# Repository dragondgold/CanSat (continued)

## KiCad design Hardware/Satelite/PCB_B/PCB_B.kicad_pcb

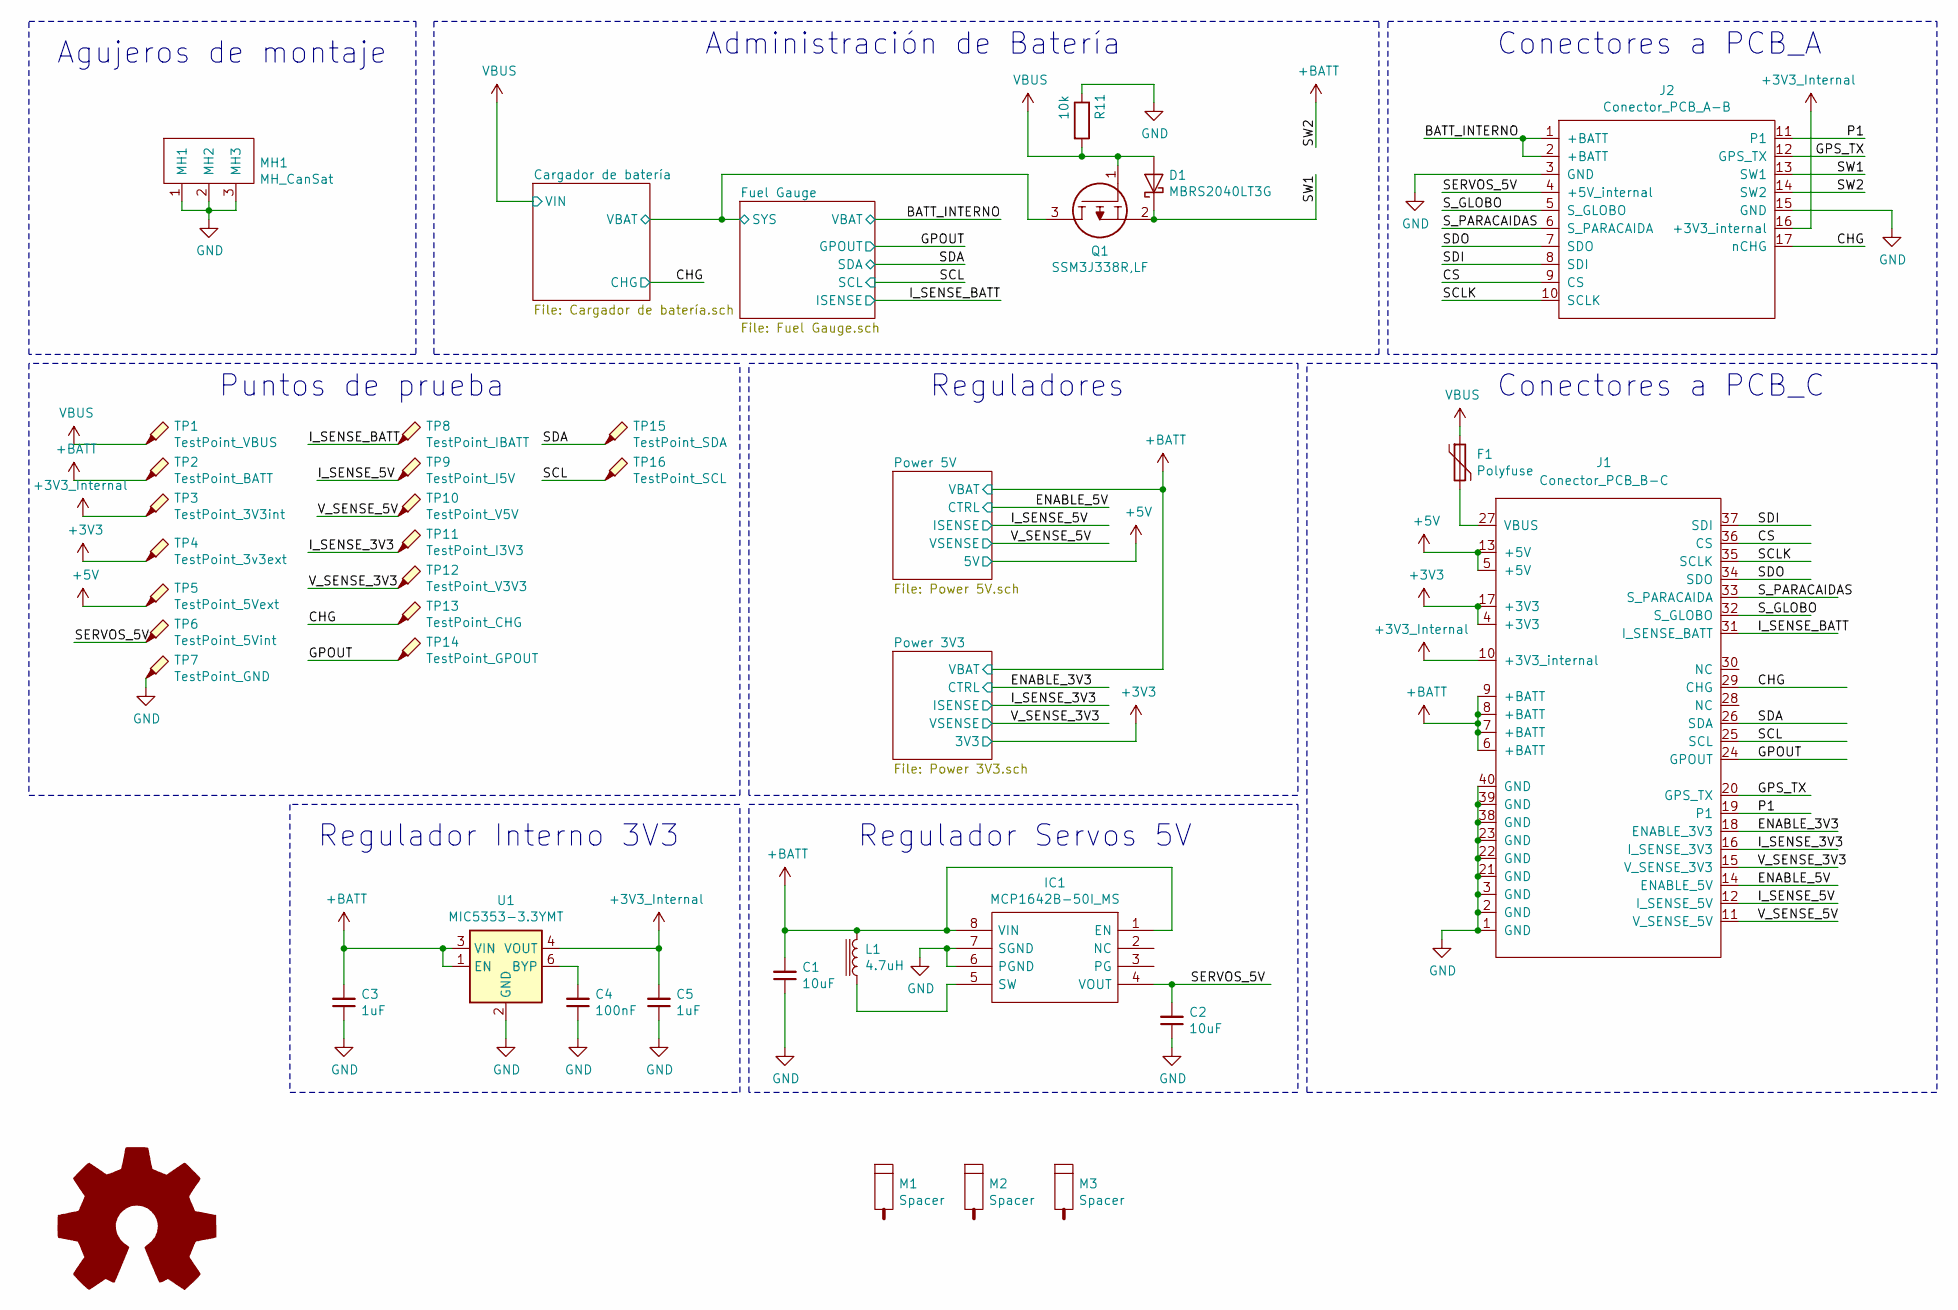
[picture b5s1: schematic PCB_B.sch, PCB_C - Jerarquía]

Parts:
C1, C2: 10uF; C_0805_2012Metric_Pad1.15x1.40mm_HandSolder; Voltage 10V; Manufacturer Part Number C2012X7R1A106M125AC
C3, C5: 1uF; C_0603_1608Metric_Pad1.05x0.95mm_HandSolder; Voltage 10V; Manufacturer Part Number LMK107B7105MA-T
C4: 100nF; C_0603_1608Metric_Pad1.05x0.95mm_HandSolder; Voltage 10V; Manufacturer Part Number EMK107B7104KAHT
D1: MBRS2040LT3G; D_SMB; Manufacturer Part Number MBRS2040LT3G
F1: Polyfuse; Fuse_1812_4532Metric_Pad1.30x3.40mm_HandSolder; Manufacturer Part Number 0ZCG0050AF2C
IC1: MCP1642B-50I_MS; SOP65P490X110-8N; Manufacturer Part Number MCP1642B-50I/MS
J1: Conector_PCB_B-C; Conector_PCB_B-C_Lado_B; Manufacturer Part Number 52465-2071
J2: Conector_PCB_A-B; Manufacturer Part Number CES-103-01-T-S
L1: 4.7uH; SRN3010TA-4R7M; Manufacturer Part Number SRN3010TA-4R7M
M1, M2, M3: Spacer; Empty_Footprint; Manufacturer Part Number R30-3011202
MH1: MH_CanSat
Q1: SSM3J338R,LF; SSM3J332RLFT; Manufacturer Part Number SSM3J338R,LF
R11: 10k; C_0603_1608Metric_Pad1.05x0.95mm_HandSolder; Manufacturer Part Number RC0603JR-0710KL
TP1: TestPoint_VBUS; TestPoint_Pad_D1.0mm
TP2: TestPoint_BATT; TestPoint_Pad_D1.0mm
TP3: TestPoint_3V3int; TestPoint_Pad_D1.0mm
TP4: TestPoint_3v3ext; TestPoint_Pad_D1.0mm
TP5: TestPoint_5Vext; TestPoint_Pad_D1.0mm
TP6: TestPoint_5Vint; TestPoint_Pad_D1.0mm
TP7: TestPoint_GND; TestPoint_THTPad_1.0x1.0mm_Drill0.5mm
TP8: TestPoint_IBATT; TestPoint_Pad_D1.0mm
TP9: TestPoint_I5V; TestPoint_Pad_D1.0mm
TP10: TestPoint_V5V; TestPoint_Pad_D1.0mm
TP11: TestPoint_I3V3; TestPoint_Pad_D1.0mm
TP12: TestPoint_V3V3; TestPoint_Pad_D1.0mm
TP13: TestPoint_CHG; TestPoint_Pad_D1.0mm
TP14: TestPoint_GPOUT; TestPoint_Pad_D1.0mm
TP15: TestPoint_SDA; TestPoint_Pad_D1.0mm
TP16: TestPoint_SCL; TestPoint_Pad_D1.0mm
U1: MIC5353-3.3YMT; MLF-6-1EP_1.6x1.6mm_P0.5mm_EP0.5x1.26mm; Manufacturer Part Number MIC5353-3.3YMT-TR

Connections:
+3V3: J1.4 (+3V3), J1.17 (+3V3), TP4.1; also elsewhere on the board
+3V3_Internal: C5.2, J1.10 (+3V3_internal), J2.16 (+3V3_internal), TP3.1, U1.4 (VOUT); also elsewhere on the board
+5V: J1.5 (+5V), J1.13 (+5V), TP5.1; also elsewhere on the board
+BATT: C1.2, C3.2, IC1.1 (EN), IC1.8 (VIN), J1.6 (+BATT), J1.7 (+BATT), J1.8 (+BATT), J1.9 (+BATT), J2.14 (SW2), L1.2, TP2.1, U1.1 (EN), U1.3 (VIN); also elsewhere on the board
/BATT_INTERNO: J2.1 (+BATT), J2.2 (+BATT); also elsewhere on the board
/CHG: J1.29 (CHG), J2.17 (nCHG), TP13.1; also elsewhere on the board
/CS: J1.36 (CS), J2.9 (CS)
/ENABLE_3V3: J1.18 (ENABLE_3V3); also elsewhere on the board
/ENABLE_5V: J1.14 (ENABLE_5V); also elsewhere on the board
/Fuel Gauge/SYS: Q1.3; also elsewhere on the board
/GPOUT: J1.24 (GPOUT), TP14.1; also elsewhere on the board
/GPS_TX: J1.20 (GPS_TX), J2.12 (GPS_TX)
/I_SENSE_3V3: J1.16 (I_SENSE_3V3), TP11.1; also elsewhere on the board
/I_SENSE_5V: J1.12 (I_SENSE_5V), TP9.1; also elsewhere on the board
/I_SENSE_BATT: J1.31 (I_SENSE_BATT), TP8.1; also elsewhere on the board
/P1: J1.19 (P1), J2.11 (P1)
/SCL: J1.25 (SCL), TP16.1; also elsewhere on the board
/SCLK: J1.35 (SCLK), J2.10 (SCLK)
/SDA: J1.26 (SDA), TP15.1; also elsewhere on the board
/SDI: J1.37 (SDI), J2.8 (SDI)
/SDO: J1.34 (SDO), J2.7 (SDO)
/SERVOS_5V: C2.2, IC1.4 (VOUT), J2.4 (+5V_internal), TP6.1
/SW1: D1.1 (K), J2.13 (SW1), Q1.2
/S_GLOBO: J1.32 (S_GLOBO), J2.5 (S_GLOBO)
/S_PARACAIDAS: J1.33 (S_PARACAIDA), J2.6 (S_PARACAIDA)
/V_SENSE_3V3: J1.15 (V_SENSE_3V3), TP12.1; also elsewhere on the board
/V_SENSE_5V: J1.11 (V_SENSE_5V), TP10.1; also elsewhere on the board
GND: C1.1, C2.1, C3.1, C4.1, C5.1, IC1.6 (PGND), IC1.7 (SGND), J1.1 (GND), J1.2 (GND), J1.3 (GND), J1.21 (GND), J1.22 (GND), J1.23 (GND), J1.38 (GND), J1.39 (GND), J1.40 (GND), J2.3 (GND), J2.15 (GND), MH1.1 (MH1), MH1.2 (MH2), MH1.3 (MH3), R11.1, TP7.1, U1.2 (GND), U1.7 (GND); also elsewhere on the board
unnamed: C4.2, U1.6 (BYP)
unnamed: F1.2, J1.27 (VBUS)
unnamed: IC1.5 (SW), L1.1
VBUS: D1.2 (A), F1.1, Q1.1, R11.2, TP1.1; also elsewhere on the board

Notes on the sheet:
Conectores a PCB_A
Reguladores
Regulador Interno 3V3
Administración de Batería
Conectores a PCB_C
Regulador Servos 5V
Agujeros de montaje
Puntos de prueba

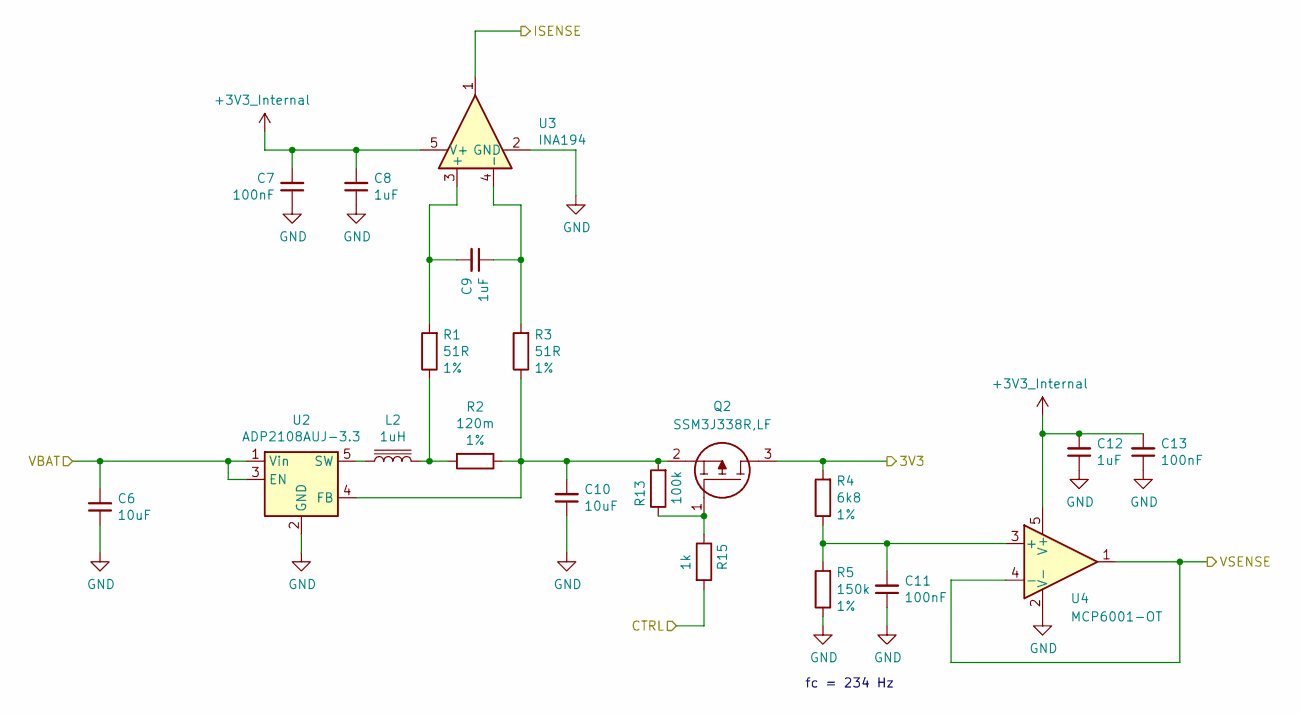
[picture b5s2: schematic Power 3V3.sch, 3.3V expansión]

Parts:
C6, C10: 10uF; C_0805_2012Metric_Pad1.15x1.40mm_HandSolder; Voltage 10V; Manufacturer Part Number C2012X7R1A106M125AC
C7, C11, C13: 100nF; C_0603_1608Metric_Pad1.05x0.95mm_HandSolder; Voltage 10V; Manufacturer Part Number EMK107B7104KAHT
C8, C9, C12: 1uF; C_0603_1608Metric_Pad1.05x0.95mm_HandSolder; Voltage 10V; Manufacturer Part Number LMK107B7105MA-T
L2: 1uH; L_0805_2012Metric_Pad1.15x1.40mm_HandSolder; Manufacturer Part Number LQM21PN1R0MC0D
Q2: SSM3J338R,LF; SSM3J332RLFT; Manufacturer Part Number SSM3J338R,LF
R1, R3: 51R; R_0603_1608Metric_Pad1.05x0.95mm_HandSolder; Tolerance 1%; Manufacturer Part Number AC0603FR-0751RL
R2: 120m; R_1206_3216Metric_Pad1.42x1.75mm_HandSolder; Tolerance 1%; Manufacturer Part Number KRL1632E-M-R120-F-T5
R4: 6k8; R_0603_1608Metric_Pad1.05x0.95mm_HandSolder; Tolerance 1%; Manufacturer Part Number RC0603FR-076K8L
R5: 150k; R_0603_1608Metric_Pad1.05x0.95mm_HandSolder; Tolerance 1%; Manufacturer Part Number RC0603FR-07150KL
R13: 100k; R_0603_1608Metric_Pad1.05x0.95mm_HandSolder; Manufacturer Part Number RC0603JR-07100KL
R15: 1k; C_0603_1608Metric_Pad1.05x0.95mm_HandSolder; Manufacturer Part Number RC0603JR-071KL
U2: ADP2108AUJ-3.3; TSOT-23-5; Manufacturer Part Number ADP2108AUJZ-3.3-R7
U3: INA194; SOT-23-5; Manufacturer Part Number INA194AIDBVR
U4: MCP6001-OT; SOT-23-5; Manufacturer Part Number MCP6001T-I/OT

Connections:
+3V3: Q2.3, R4.2; also elsewhere on the board
+3V3_Internal: C7.2, C8.2, C12.2, C13.2, U3.5 (V+), U4.5 (V+); also elsewhere on the board
+BATT: C6.2, U2.1 (Vin), U2.3 (EN); also elsewhere on the board
/ENABLE_3V3: R15.2; also elsewhere on the board
/I_SENSE_3V3: U3.1; also elsewhere on the board
/V_SENSE_3V3: U4.1, U4.4 (-); also elsewhere on the board
GND: C6.1, C7.1, C8.1, C10.1, C11.1, C12.1, C13.1, R5.1, U2.2 (GND), U3.2 (GND), U4.2 (V-); also elsewhere on the board
unnamed: C9.1, R3.2, U3.4 (-)
unnamed: C9.2, R1.2, U3.3 (+)
unnamed: C10.2, Q2.2, R2.1, R3.1, R13.2, U2.4 (FB)
unnamed: C11.2, R4.1, R5.2, U4.3 (+)
unnamed: L2.1, U2.5 (SW)
unnamed: L2.2, R1.1, R2.2
unnamed: Q2.1, R13.1, R15.1

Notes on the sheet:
fc = 234 Hz

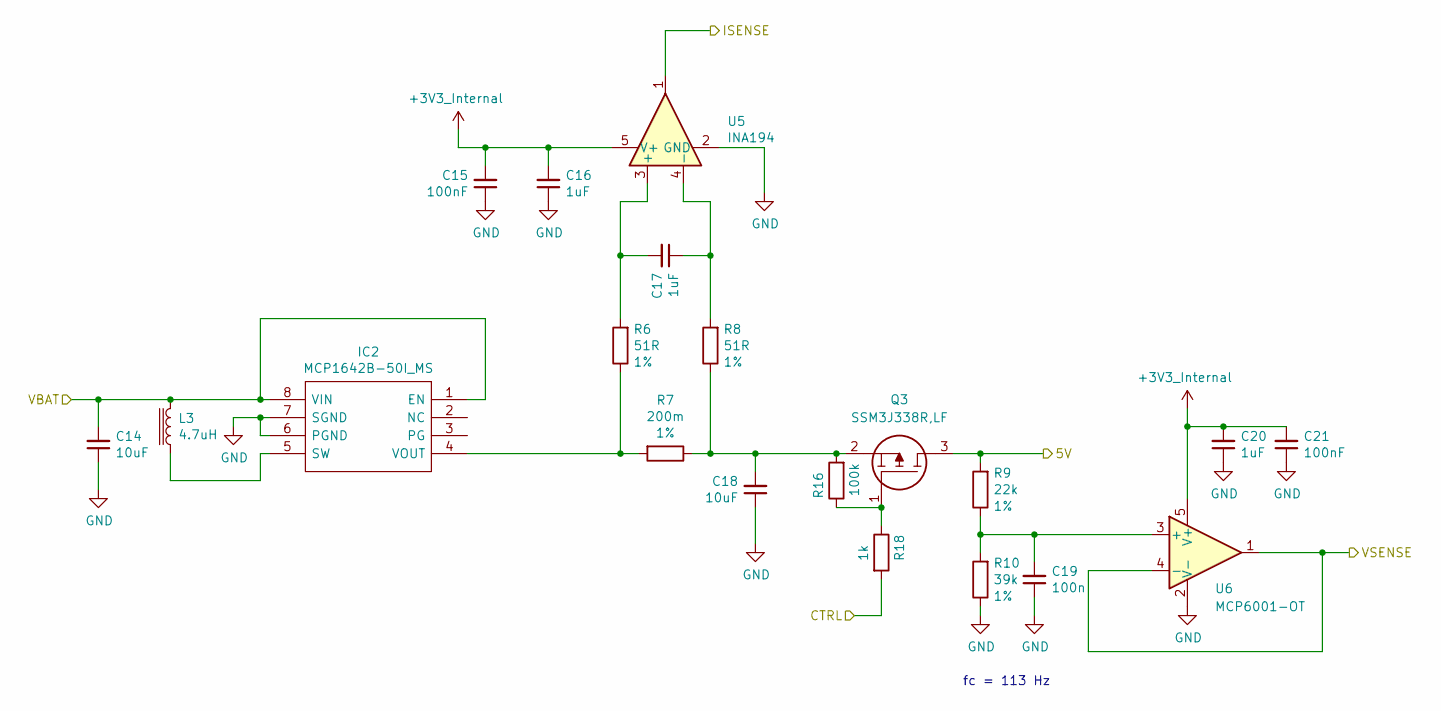
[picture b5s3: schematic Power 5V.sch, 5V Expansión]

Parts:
C14, C18: 10uF; C_0805_2012Metric_Pad1.15x1.40mm_HandSolder; Voltage 10V; Manufacturer Part Number C2012X7R1A106M125AC
C15, C21: 100nF; C_0603_1608Metric_Pad1.05x0.95mm_HandSolder; Voltage 10V; Manufacturer Part Number EMK107B7104KAHT
C16, C17, C20: 1uF; C_0603_1608Metric_Pad1.05x0.95mm_HandSolder; Voltage 10V; Manufacturer Part Number LMK107B7105MA-T
C19: 100n; C_0603_1608Metric_Pad1.05x0.95mm_HandSolder; Voltage 10V; Manufacturer Part Number EMK107B7104KAHT
IC2: MCP1642B-50I_MS; SOP65P490X110-8N; Manufacturer Part Number MCP1642B-50I/MS
L3: 4.7uH; SRN3010TA-4R7M; Manufacturer Part Number SRN3010TA-4R7M
Q3: SSM3J338R,LF; SSM3J332RLFT; Manufacturer Part Number SSM3J338R,LF
R6, R8: 51R; R_0603_1608Metric_Pad1.05x0.95mm_HandSolder; Tolerance 1%; Manufacturer Part Number AC0603FR-0751RL
R7: 200m; R_1206_3216Metric_Pad1.42x1.75mm_HandSolder; Tolerance 1%; Manufacturer Part Number KRL1632E-C-R200-F-T5
R9: 22k; R_0603_1608Metric_Pad1.05x0.95mm_HandSolder; Tolerance 1%; Manufacturer Part Number RC0603FR-1322KL
R10: 39k; R_0603_1608Metric_Pad1.05x0.95mm_HandSolder; Tolerance 1%; Manufacturer Part Number RC0603FR-1339KL
R16: 100k; R_0603_1608Metric_Pad1.05x0.95mm_HandSolder; Manufacturer Part Number RC0603JR-07100KL
R18: 1k; C_0603_1608Metric_Pad1.05x0.95mm_HandSolder; Manufacturer Part Number RC0603JR-071KL
U5: INA194; SOT-23-5; Manufacturer Part Number INA194AIDBVR
U6: MCP6001-OT; SOT-23-5; Manufacturer Part Number MCP6001T-I/OT

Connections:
+3V3_Internal: C15.2, C16.2, C20.2, C21.2, U5.5 (V+), U6.5 (V+); also elsewhere on the board
+5V: Q3.3, R9.2; also elsewhere on the board
+BATT: C14.2, IC2.1 (EN), IC2.8 (VIN), L3.2; also elsewhere on the board
/ENABLE_5V: R18.2; also elsewhere on the board
/I_SENSE_5V: U5.1; also elsewhere on the board
/V_SENSE_5V: U6.1, U6.4 (-); also elsewhere on the board
GND: C14.1, C15.1, C16.1, C18.1, C19.1, C20.1, C21.1, IC2.6 (PGND), IC2.7 (SGND), R10.1, U5.2 (GND), U6.2 (V-); also elsewhere on the board
unnamed: C17.1, R8.2, U5.4 (-)
unnamed: C17.2, R6.2, U5.3 (+)
unnamed: C18.2, Q3.2, R7.1, R8.1, R16.2
unnamed: C19.2, R9.1, R10.2, U6.3 (+)
unnamed: IC2.4 (VOUT), R6.1, R7.2
unnamed: IC2.5 (SW), L3.1
unnamed: Q3.1, R16.1, R18.1

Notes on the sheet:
fc = 113 Hz

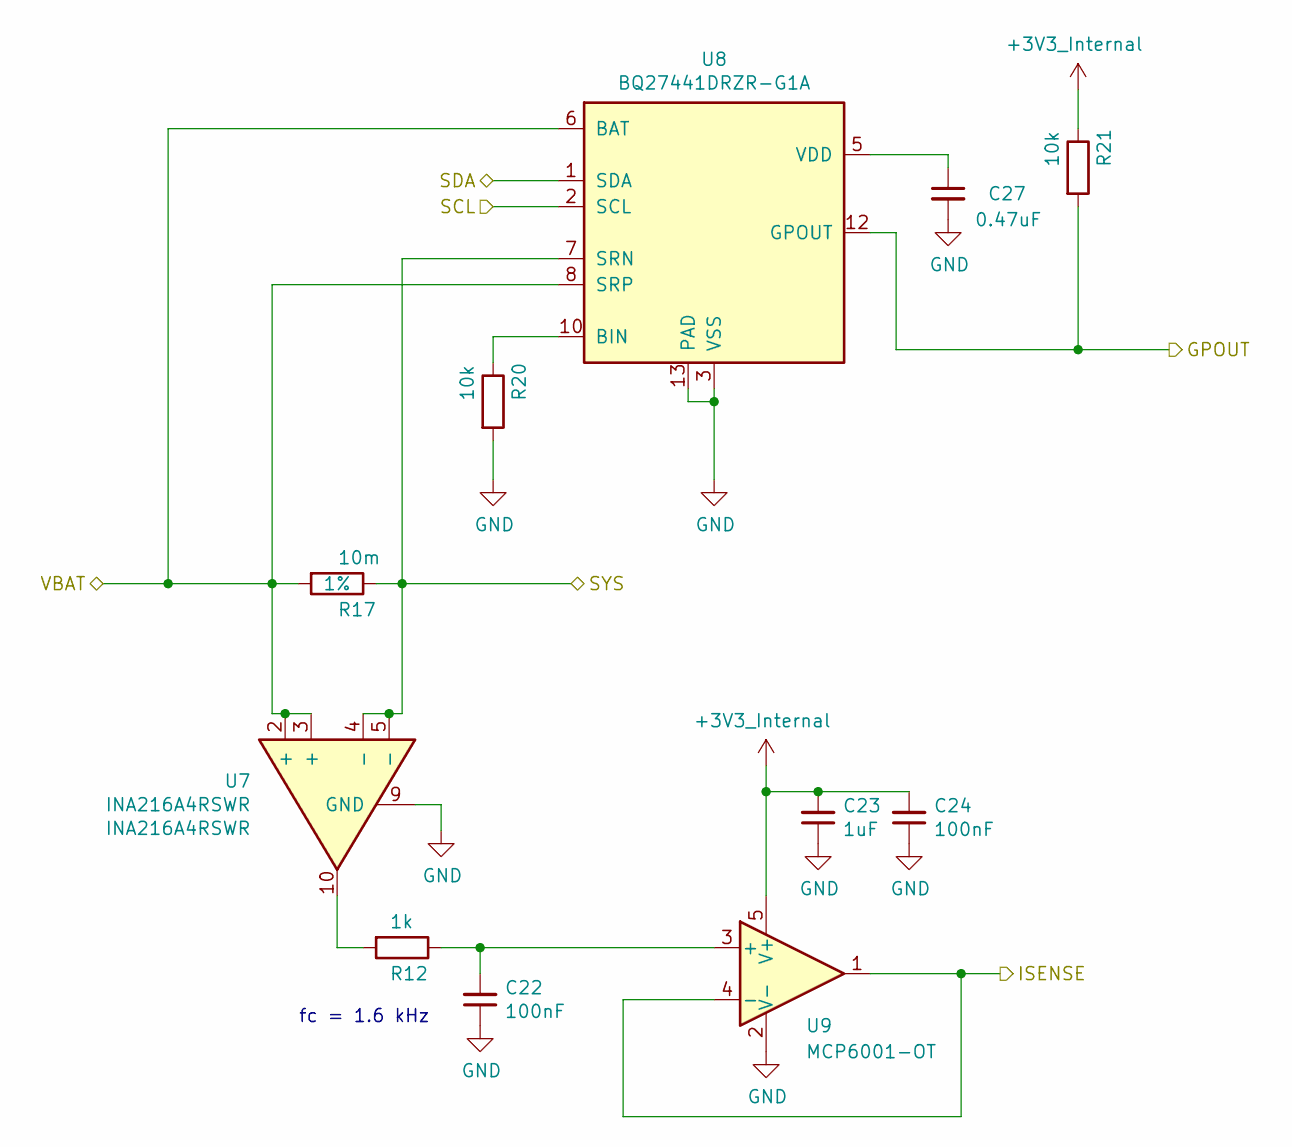
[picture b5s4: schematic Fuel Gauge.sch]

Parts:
C22, C24: 100nF; C_0603_1608Metric_Pad1.05x0.95mm_HandSolder; Voltage 10V; Manufacturer Part Number EMK107B7104KAHT
C23: 1uF; C_0603_1608Metric_Pad1.05x0.95mm_HandSolder; Voltage 10V; Manufacturer Part Number LMK107B7105MA-T
C27: 0.47uF; C_0603_1608Metric_Pad1.05x0.95mm_HandSolder; Manufacturer Part Number 885012206024
R12: 1k; C_0603_1608Metric_Pad1.05x0.95mm_HandSolder; Manufacturer Part Number RC0603JR-071KL
R17: 10m; R_2512_6332Metric_Pad1.52x3.35mm_HandSolder; Tolerance 1%; Manufacturer Part Number KRL3264-C-R010-F-T1
R20, R21: 10k; C_0603_1608Metric_Pad1.05x0.95mm_HandSolder; Manufacturer Part Number RC0603JR-0710KL
U7: INA216A4RSWR; UQFN-10_1.3x1.8mm_P0.4mm; Manufacturer Part Number INA216A4RSWR
U8: BQ27441DRZR-G1A; Texas_S-PDSO-N12; Manufacturer Part Number BQ27441DRZR-G1A
U9: MCP6001-OT; SOT-23-5; Manufacturer Part Number MCP6001T-I/OT

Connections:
+3V3_Internal: C23.2, C24.2, R21.1, U9.5 (V+); also elsewhere on the board
/BATT_INTERNO: R17.2, U7.2 (+), U7.3 (+), U8.6 (BAT), U8.8 (SRP); also elsewhere on the board
/Fuel Gauge/SYS: R17.1, U7.4 (-), U7.5 (-), U8.7 (SRN); also elsewhere on the board
/GPOUT: R21.2, U8.12 (GPOUT); also elsewhere on the board
/I_SENSE_BATT: U9.1, U9.4 (-); also elsewhere on the board
/SCL: U8.2 (SCL); also elsewhere on the board
/SDA: U8.1 (SDA); also elsewhere on the board
GND: C22.1, C23.1, C24.1, C27.2, R20.2, U7.9 (GND), U8.3 (VSS), U8.13 (PAD), U9.2 (V-); also elsewhere on the board
unnamed: C22.2, R12.1, U9.3 (+)
unnamed: C27.1, U8.5 (VDD)
unnamed: R12.2, U7.10
unnamed: R20.1, U8.10 (BIN)

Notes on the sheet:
fc = 1.6 kHz

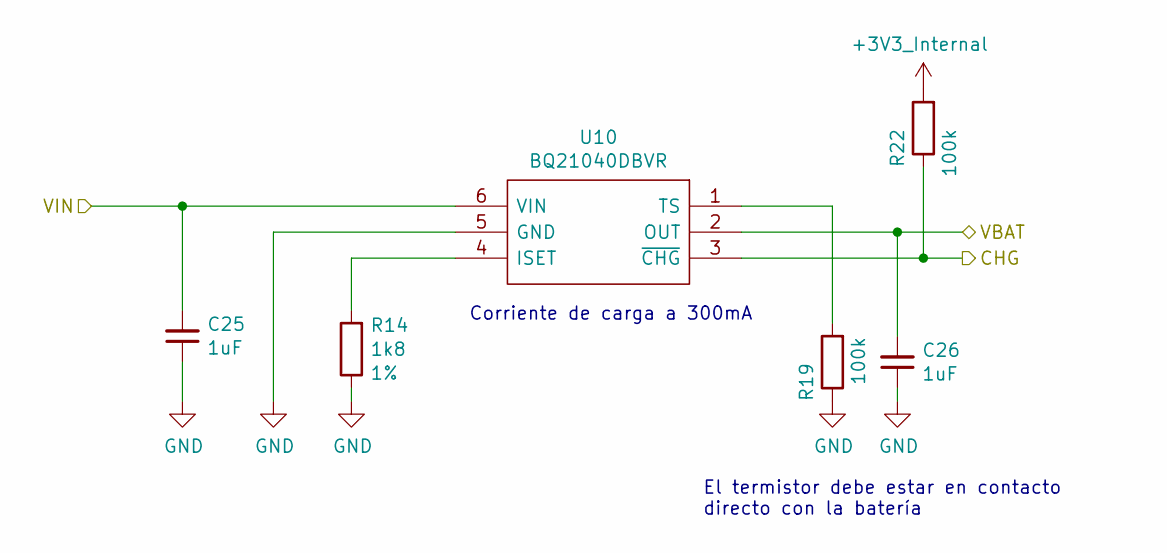
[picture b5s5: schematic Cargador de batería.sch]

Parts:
C25, C26: 1uF; C_0603_1608Metric_Pad1.05x0.95mm_HandSolder; Voltage 10V; Manufacturer Part Number LMK107B7105MA-T
R14: 1k8; R_0603_1608Metric_Pad1.05x0.95mm_HandSolder; Tolerance 1%; Manufacturer Part Number RC0603FR-071K8L
R19, R22: 100k; R_0603_1608Metric_Pad1.05x0.95mm_HandSolder; Manufacturer Part Number RC0603JR-07100KL
U10: BQ21040DBVR; SOT95P280X145-6N; Manufacturer_Part_Number BQ21040DBVR; Mouser Part Number 595-BQ21040DBVR

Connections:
+3V3_Internal: R22.2; also elsewhere on the board
/CHG: R22.1, U10.3 (~CHG); also elsewhere on the board
/Fuel Gauge/SYS: C26.2, U10.2 (OUT); also elsewhere on the board
GND: C25.1, C26.1, R14.1, R19.1, U10.5 (GND); also elsewhere on the board
unnamed: R14.2, U10.4 (ISET)
unnamed: R19.2, U10.1 (TS)
VBUS: C25.2, U10.6 (VIN); also elsewhere on the board

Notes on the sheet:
Corriente de carga a 300mA
El termistor debe estar en contacto directo con la batería

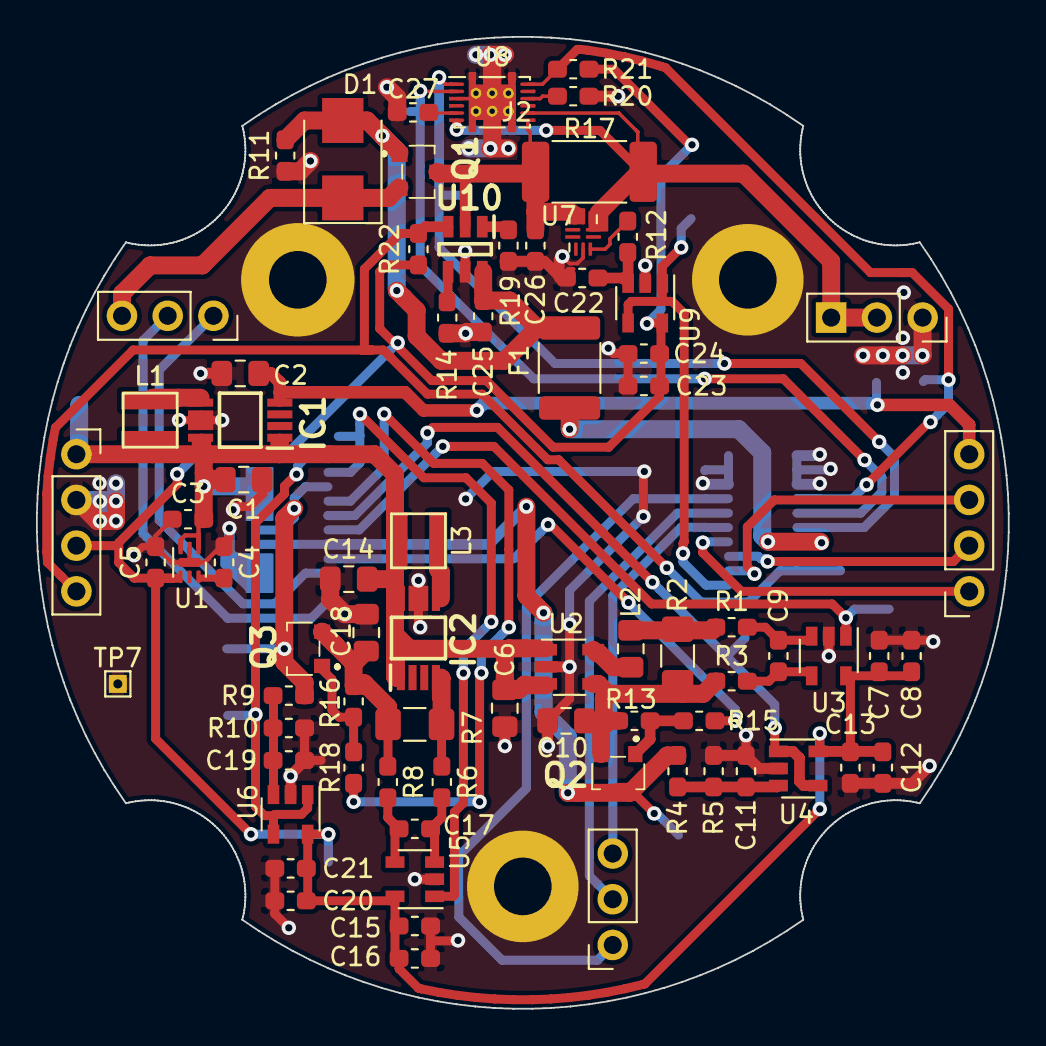
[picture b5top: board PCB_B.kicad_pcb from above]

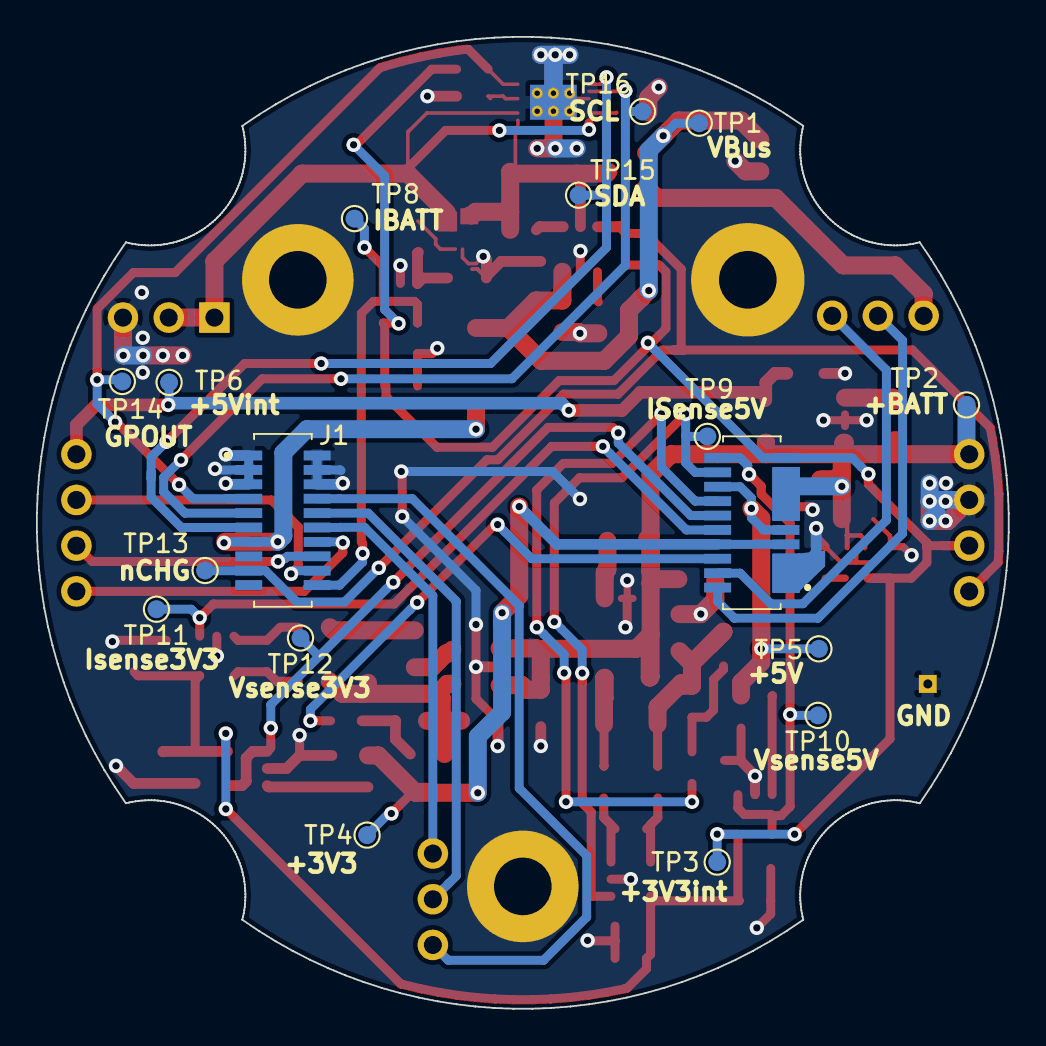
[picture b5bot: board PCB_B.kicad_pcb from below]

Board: 2 copper layers, 54.0 x 54.0 mm, 91 parts (15 on the bottom side), 52 nets.

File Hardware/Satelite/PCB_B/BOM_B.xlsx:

Qty | Reference(s) | Value | Footprint | Manufacturer Part Number
6 | C1, C2, C6, C10, C14, C18 | 10uF | Capacitor_SMD:C_0805_2012Metric_Pad1.15x1.40mm_HandSolder | C2012X7R1A106M125AC
11 | C3, C5, C8, C9, C12, C16, C17, C20, C23, C25, C26 | 1uF | Capacitor_SMD:C_0603_1608Metric_Pad1.05x0.95mm_HandSolder | LMK107B7105MA-T
8 | C4, C7, C11, C13, C15, C21, C22, C24 | 100nF | Capacitor_SMD:C_0603_1608Metric_Pad1.05x0.95mm_HandSolder | EMK107B7104KAHT
1 | C19 | 100n | Capacitor_SMD:C_0603_1608Metric_Pad1.05x0.95mm_HandSolder | EMK107B7104KAHT
1 | C27 | 0.47uF | Capacitor_SMD:C_0603_1608Metric_Pad1.05x0.95mm_HandSolder | 885012206024
1 | D1 | MBRS2040LT3G | Diode_SMD:D_SMB | MBRS2040LT3G
1 | F1 | Polyfuse | Fuse:Fuse_1812_4532Metric_Pad1.30x3.40mm_HandSolder | 0ZCG0050AF2C
2 | IC1, IC2 | MCP1642B-50I_MS | SamacSys_Parts:SOP65P490X110-8N | MCP1642B-50I/MS
1 | J1 | Conector_PCB_B-C | AXTEC:Conector_PCB_B-C_Lado_B | 52465-2071
3 | J2 | Conector_PCB_A-B | AXTEC:Conector_PCB_A-B | CES-103-01-T-S
2 | J2 | Conector_PCB_A-B | AXTEC:Conector_PCB_A-B | CES-104-01-T-S
2 | L1, L3 | 4.7uH | AXTEC:SRN3010TA-4R7M | SRN3010TA-4R7M
1 | L2 | 1uH | Inductor_SMD:L_0805_2012Metric_Pad1.15x1.40mm_HandSolder | LQM21PN1R0MC0D
3 | M1, M2, M3 | Spacer | AXTEC:Empty_Footprint | R30-3001202
1 | MH1 | MH_CanSat | AXTEC:MH_CanSat
3 | Q1, Q2, Q3 | SSM3J338R,LF | SamacSys_Parts:SSM3J332RLFT | SSM3J338R,LF
4 | R1, R3, R6, R8 | 51R | Resistor_SMD:R_0603_1608Metric_Pad1.05x0.95mm_HandSolder | AC0603FR-0751RL
1 | R2 | 120m | Resistor_SMD:R_1206_3216Metric_Pad1.42x1.75mm_HandSolder | KRL1632E-M-R120-F-T5
1 | R4 | 6k8 | Resistor_SMD:R_0603_1608Metric_Pad1.05x0.95mm_HandSolder | RC0603FR-076K8L
1 | R5 | 150k | Resistor_SMD:R_0603_1608Metric_Pad1.05x0.95mm_HandSolder | RC0603FR-07150KL
1 | R7 | 200m | Resistor_SMD:R_1206_3216Metric_Pad1.42x1.75mm_HandSolder | KRL1632E-C-R200-F-T5
1 | R9 | 22k | Resistor_SMD:R_0603_1608Metric_Pad1.05x0.95mm_HandSolder | RC0603FR-1322KL
1 | R10 | 39k | Resistor_SMD:R_0603_1608Metric_Pad1.05x0.95mm_HandSolder | RC0603FR-1339KL
4 | R11, R19, R20, R21 | 10k | Capacitor_SMD:C_0603_1608Metric_Pad1.05x0.95mm_HandSolder | RC0603JR-0710KL
3 | R12, R15, R18 | 1k | Capacitor_SMD:C_0603_1608Metric_Pad1.05x0.95mm_HandSolder | RC0603JR-071KL
3 | R13, R16, R22 | 100k | Resistor_SMD:R_0603_1608Metric_Pad1.05x0.95mm_HandSolder | RC0603JR-07100KL
1 | R14 | 1k8 | Resistor_SMD:R_0603_1608Metric_Pad1.05x0.95mm_HandSolder | RC0603FR-071K8L
1 | R17 | 10m | Resistor_SMD:R_2512_6332Metric_Pad1.52x3.35mm_HandSolder | KRL3264-C-R010-F-T1
1 | U1 | MIC5353-3.3YMT | Package_DFN_QFN:MLF-6-1EP_1.6x1.6mm_P0.5mm_EP0.5x1.26mm | MIC5353-3.3YMT-TR
1 | U2 | ADP2108AUJ-3.3 | Package_TO_SOT_SMD:TSOT-23-5 | ADP2108AUJZ-3.3-R7
2 | U3, U5 | INA194 | Package_TO_SOT_SMD:SOT-23-5 | INA194AIDBVR
3 | U4, U6, U9 | MCP6001-OT | Package_TO_SOT_SMD:SOT-23-5 | MCP6001T-I/OT
1 | U7 | INA216A4RSWR | Package_DFN_QFN:UQFN-10_1.3x1.8mm_P0.4mm | INA216A4RSWR
1 | U8 | BQ27441DRZR-G1A | Package_SON:Texas_S-PDSO-N12 | BQ27441DRZR-G1A
1 | U10 | BQ21040DBVR | SamacSys_Parts:SOT95P280X145-6N | BQ21040DBVR

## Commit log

2019-04-30 Arreglos en PCB_A y PCB_B:
    - El CI cargador de batería ya no alimenta al sistema, al conectar un cargador el mismo alimenta a la batería y al sistema de manera simultánea
    - Ya no es necesario encender el CanSat para cargar la batería
    - El interruptor del PCB_A ahora apaga todo el sistema independientemente si se está cargando o no la batería
    - Agregado LED indicador de carga de batería
2019-04-30 Agregado circuito de protección para batería en PCB_A
2019-04-30 Agregadas librerías a PCB_C y renombrados pines no usado en el conector B-C
2019-04-30 Eliminado circuito de detección de cargador de PCB_C, siempre usamos toda la corriente de carga ahora.
2019-04-30 Agregado de MOSFET para cortar las fuentes de 3.3V y 5V en el PCB_B en lugar de usar los enable
2019-04-30 Espaciadores más largos para PCB que usan conector de expansión
2019-04-30 Corregido MOSFET Q1 con drenador y surtidor invertidos
2019-04-30 Nuevo conector entre PCB_B y PCB_C, más fácil de soldar y robusto
2019-04-30 ESP32 tamaño compacto sin antena PCB
2019-05-01 Agregado conversor USB-Serie en PCB_C para poder programar el ESP32 desde USB
2019-05-01 Cambio de MCU de ESP32 a nRF52840
2019-05-01 Eliminación de wires no usadas en esquema de PCB_C
2019-05-01 Fixed wrong label in fuel gauge schematic
2019-05-01 Arreglo de mosfet en PCB_B
2019-05-01 Nuevos buffers bidireccionales en PCB_C. Deberían solucionar los problemas que existían con los antiguos buffers que eran muy sensibles a cualquier carga que se colocara (analizador lógico por ejempl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
2019-05-01 Agregado conector de programación para el nRF52840
2019-05-01 Agregados R pull-down en buffers del PCB_C
2019-05-02 Agregado extensor de rango CC1190 en PCB_A
2019-05-02 Agregado sensor de temperatura de mayor precisión
2019-05-02 Eliminada referencia de tensión no usada en PCB_C
2019-05-02 Agregado footprints faltantes en PCB_C
2019-05-02 Cambiado el nombre de la carpeta de liberías KiCad para no tener espacios ya que da problemas
2019-05-02 Agregados footprints faltantes en samacsys + asignacion en PCB_C
2019-05-02 Cambiado pin "A1" por "0" en footprint BL654
2019-05-02 Netlist para PCB_C
2019-05-02 PCB de PCB_A (WIP)
2019-05-02 Completado nuevo PCB_A
2019-05-04 Mejoras al layout RF de PCB_A
2019-05-05 Corrección de librerías en PCB de estación terrena
2019-05-05 Agregado CC1190 a estación terrena
2019-05-05 PCB_C V2 terminado
2019-05-05 Estacion terrena:
    - Nuevo LDO de 500mA para poder utilizar el CC1190 a toda su potencia de ser necesario
    - Cambiado el MCP2210 por un PIC18F14K50 ya que el MCP2210 es MUY lento para transferencias SPI
    - Agregado de footprints faltantes
2019-05-06 Nuevo PCB de estación terrena con CC1190
2019-05-06 Pequeñas mejoras a PCB_C
2019-05-06 Nuevo LDO de más corriente para 3.3V internos en PCB_B
2019-05-06 Corrección de silkscreen PCB_C
2019-05-06 Nuevo footprint de conector B-C en lado B
2019-05-06 Agregados silkscreen faltantes en estación terrena
2019-05-06 PCB_D:
    - Corregidas librerías
    - Agregado diodo para poder alimentar el Arduino tanto cuando esta solo como cuando se encuentra en el stack del CanSat
2019-05-07 Conectores con más altura y nuevos separadores en PCB_C
2019-05-07 Agregado de modelos 3D a PCB_C
2019-05-07 Movido el conector USB más afuera en PCB_D
2019-05-07 Nuevo modelo 3D para satélite
2019-05-08 PCB_B V2 terminado
2019-05-08 PCB_B plano de masa mejorado
2019-05-08 Correcciones en conector B-C lado B
2019-05-08 Nuevos separadores en PCB_B
2019-05-08 Corrección del pin nRST mal ubicado en PCB_C
2019-05-08 Reducido el tamaño del PAD central para CC1190
2019-05-08 Corrección pin nRST en PCB_C kicad_pcb
2019-05-08 Centrado de apertura de conectores USB con aperturas laterales en estructura mecánica del satélite
2019-05-08 Nuevos conectores micro-usb completamente SMD
2019-05-08 Eliminidas tiras de pines en PCB_A para conexión de servos, se sueldan los cables directamente al PCB
2019-05-08 Eliminado termistor de PCB_B
2019-05-08 Agregado jumper de selección de ganancia para CC1190 en ET
2019-05-08 Nuevo conector USB para ET
2019-05-08 Agregado jumper de seleción de ganacia para CC1190 en ET
2019-05-15 Movidos LEDs de TX y RX en PCB_D al lado del USB para que sean más visibles
2019-05-15 Agregado nuevo soporte para antena
2019-05-15 Agregado más pines y corrección de distancia entre pines en PCB_E
2019-05-15 Agregado de logos faltantes en PCB_A
2019-05-15 Agregado de logos faltantes en PCB_B
2019-05-15 Agregado de logos faltantes en PCB_C
2019-05-15 Eliminado modelo 3D en PCB_E
2019-05-15 Agregado transistor para led en SCK PCB_D + correcciones de silkscreen
2019-05-25 Removidos componentes duplicados en SamacSys_Part
2019-06-21 Arreglo de trazas en PCB_C
2019-06-21 Pequeños arreglos a silkscreen en PCB_A
2019-06-21 Agregado logo faltante en PCB_D
2019-06-21 Nuevos gerbers generados para todos los PCB
2019-06-21 Agregado indicadores de pin 1 faltantes
2019-06-23 Nuevos gerbers para PCB_C
2019-06-25 Eliminado antiguo PCB de antena
2019-06-25 PCB_A BOM
2019-06-25 PCB_B BOM
2019-06-25 PCB_C BOM
2019-06-25 PCB_D BOM
2019-06-25 PCB_E BOM
2019-06-25 Estación terrena BOM
2019-06-25 Arreglo de errores en BOM de B y C
2019-06-26 Regulador de 3.3V independiente para PCB_D
2019-08-08 Corregido número de parte de conector B-C en PCB_C
2019-09-27 Removido boton de agregar muestra para testear graficos
2019-09-29 Código inicial para librería Arduino
2019-10-02 Cambios en librería Arduino y ejemplo
2020-03-07 Initial code for firmware version 2.0 running on the nRF52
2020-03-08 Added new spi_manager with improved capabilities compared to the one implemented in the ESP32
2020-03-14 Bump lodash.defaultsdeep from 4.6.0 to 4.6.1 in /desktop-app
    Bumps [lodash.defaultsdeep](https://github.com/lodash/lodash) from 4.6.0 to 4.6.1.
    - [Release notes](https://github.com/lodash/lodash/releases)
    - [Commits](https://github.com/lodash/lodash/compare/4.6.0...4.6.1)
2020-03-14 Bump lodash.mergewith from 4.6.1 to 4.6.2 in /desktop-app
    Bumps [lodash.mergewith](https://github.com/lodash/lodash) from 4.6.1 to 4.6.2.
    - [Release notes](https://github.com/lodash/lodash/releases)
    - [Commits](https://github.com/lodash/lodash/commits)
2020-03-14 Added time_manager
2020-03-14 Bump lodash from 4.17.11 to 4.17.15 in /desktop-app
    Bumps [lodash](https://github.com/lodash/lodash) from 4.17.11 to 4.17.15.
    - [Release notes](https://github.com/lodash/lodash/releases)
    - [Commits](https://github.com/lodash/lodash/compare/4.17.11...4.17.15)
2020-03-14 Bump lodash.merge from 4.6.1 to 4.6.2 in /desktop-app
    Bumps [lodash.merge](https://github.com/lodash/lodash) from 4.6.1 to 4.6.2.
    - [Release notes](https://github.com/lodash/lodash/releases)
    - [Commits](https://github.com/lodash/lodash/commits)
2020-03-14 Bump mixin-deep from 1.3.1 to 1.3.2 in /desktop-app
    Bumps [mixin-deep](https://github.com/jonschlinkert/mixin-deep) from 1.3.1 to 1.3.2.
    - [Release notes](https://github.com/jonschlinkert/mixin-deep/releases)
    - [Commits](https://github.com/jonschlinkert/mixin-deep/compare/1.3.1...1.3.2)
2020-03-14 Bump npm from 6.4.1 to 6.14.2 in /desktop-app
    Bumps [npm](https://github.com/npm/cli) from 6.4.1 to 6.14.2.
    - [Release notes](https://github.com/npm/cli/releases)
    - [Changelog](https://github.com/npm/cli/blob/latest/CHANGELOG.md)
    - [Commits](https://github.com/npm/cli/compare/v6.4.1...v6.14.2)
2020-03-15 Added battery_manager with proper HAL to make it ALMOST platform independent (the logging library is not decoupled yet)
2020-05-01 WIP driver for BQ27441
